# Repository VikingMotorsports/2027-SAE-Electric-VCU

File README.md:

# Formula SAE EV Vehicle Control System

A distributed **Vehicle Control System (VCS)** for a Formula SAE Electric racecar. The system uses STM32 microcontrollers running Zephyr RTOS for real-time vehicle control, a CAN bus for communication, and a Raspberry Pi for driver and remote telemetry displays.

> **Status:** Active Development

---

## System Overview

The VCS is currently built around two **STM32C092** modules and a Raspberry Pi.

- **Pedal Input Module** — Reads accelerator and brake pedal inputs and transmits them over CAN.
- **Motor Controller Module** — Receives pedal commands over CAN and generates PWM signals for the motor H-bridge.
- **Raspberry Pi Dashboard** — Receives CAN data and displays accelerator and brake inputs to the driver.
- **Remote Pit Dashboard** — Receives vehicle data from the Raspberry Pi over MQTT.

### Architecture

```text

     ┌──────────────────────┐			┌──────────────────────┐
     │   Brake Pedal        │			│   Accelerator Pedal  │
     └──────────┬───────────┘			└──────────┬───────────┘
				│								   │
				└─────────────────┬────────────────┘
                                  │
                                  ▼
                    ┌──────────────────────────┐
                    │   STM32C092              │
                    │   Pedal Input Module     │
                    │                          │
                    │   Zephyr RTOS            │
                    │   ADC → CAN              │
                    └────────────┬─────────────┘
                                 │
                                 │ CAN Bus
                                 │
                ┌────────────────┴────────────────┐
                │                                 │
                ▼                                 ▼
     ┌──────────────────────┐          ┌──────────────────────┐
     │   STM32C092          │          │   Raspberry Pi       │
     │   Motor Controller   │          │   Dashboard          │
     │                      │          │                      │
     │   CAN → PWM          │          │   CAN → Display      │
     └──────────┬───────────┘          └──────────┬───────────┘
                │                                 │
                │ PWM / Control                   │ MQTT
                ▼                                 ▼
     ┌──────────────────────┐          ┌──────────────────────┐
     │   Motor H-Bridge     │          │   Remote Pit         │
     │                      │          │   Dashboard          │
     └──────────────────────┘          └──────────────────────┘

````

---

## Hardware & Software

| Component        | Description                                                |
| ---------------- | ---------------------------------------------------------- |
| **STM32C092**    | Embedded vehicle control modules                           |
| **Zephyr RTOS**  | Real-time operating system for STM32 modules               |
| **CAN Bus**      | Communication between vehicle modules                      |
| **Raspberry Pi** | Dashboard and vehicle telemetry gateway                    |
| **Vulcan**       | CAN interface between the vehicle network and Raspberry Pi |
| **MQTT**         | Remote telemetry communication                             |
| **KiCad**        | Electrical and PCB design                                  |

---

## Repository Structure

```text
.
├── Dashboard/              # Raspberry Pi driver dashboard
├── Dashboard Webdisplay/   # Remote pit dashboard
├── Developers_Guide/       # Development documentation
├── PCB/                  	# PCB and electrical design files
├── MQTT/                   # MQTT communication
├── Vulcan/                 # CAN interface and configuration
├── Zephyr_apps/            # STM32C092 Zephyr applications
├── Zephyr_Scripts/         # Build, flash, and development scripts
├── .gitignore
└── README.md
```

---

## Communication

### CAN

The STM32 modules communicate over CAN. The Pedal Input Module sends accelerator and brake values to the CAN network, where they are received by the Motor Controller Module and Raspberry Pi.

```text
Pedal Module
     │
     ├── Accelerator
     └── Brake
          │
          ▼
       CAN Bus
       ┌────┴────┐
       ▼         ▼
Motor Controller  Raspberry Pi
       │             │
       ▼             ├──> Driver Dashboard
    PWM              │
       │             └──> MQTT
       ▼                    │
   H-Bridge                 ▼
                     Remote Pit Dashboard
```

### MQTT

The Raspberry Pi republishes selected CAN data over MQTT, allowing the pit crew to monitor vehicle information remotely.

---

## Current Functionality

The current system provides an end-to-end control and telemetry path:

* Accelerator and brake inputs are read by the Pedal Input Module.
* Pedal values are transmitted over CAN.
* The Motor Controller receives the commands and generates PWM output.
* The Raspberry Pi receives and displays pedal data on the driver dashboard.
* The Raspberry Pi broadcasts the same data over MQTT.
* A remote pit dashboard displays the transmitted vehicle data.

---

## Development

The system is designed to be modular, allowing additional vehicle control and monitoring functionality to be added as development continues.

### Planned Development

* [ ] Expand vehicle telemetry
* [ ] Add additional CAN messages
* [ ] Expand driver dashboard
* [ ] Expand remote pit monitoring
* [ ] Implement fault detection and reporting
* [ ] Add vehicle safety interlocks
* [ ] Develop dedicated VCS hardware
* [ ] Improve CAN diagnostics and logging
* [ ] Complete system-level testing

---

## Project Status

**Early Development / System Integration**

The basic vehicle control and telemetry pipeline is currently operational:

```text
Pedals
  ↓
STM32 Pedal Module
  ↓
CAN Bus
  ├──> STM32 Motor Controller ──> PWM ──> H-Bridge
  │
  └──> Raspberry Pi
          ├──> Driver Dashboard
          │
          └──> MQTT ──> Remote Pit Dashboard
```

Developed as part of a **Formula SAE Electric** racecar project.

```
```

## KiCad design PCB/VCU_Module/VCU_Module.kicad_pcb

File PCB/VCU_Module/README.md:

---
title: "**Viking MotorSports VCU Module**"
subtitle: |
  **Fabrication and Assembly Information**\
  For build TIME-STAMP
fontsize: 10pt
geometry:
  - margin=0.5in
toc: true
toc-depth: 2
colorlinks: true
urlcolor: blue
---

\newpage

# About this Board

## Board Description

## Documentation Links

## Documentation Files

| Filename                        | Notes                                    |
| ------------------------------- | ---------------------------------------- |
| README.pdf                      | This README file                         |
| VCU_Module-outline.dxf        | Board outline (with holes) in DXF format |
| VCU_Module-pcba.step          | 3D model of PCBA (with components)       |
| VCU_Module-render-bot.jpg     | Render of the top of the 3D model        |
| VCU_Module-render-bot.jpg     | Render of the bottom of the 3D model     |
| VCU_Module-schematic.pdf      | PDF of board schematics                  |

## Contact Information

- Website: *website*
- Email: *email*

## Board Renders

\newpage

# Printed Circuit Board (PCB) Fabrication Information

## Board Info

- 2 layer board
- Bounding box is *TBD*
- Board thickness is 1.59 mm (0.063 inch)

## Board Requirements

- Design Rules
    - Minimum Trace / Space design rulea: 0.1524 mm (6.0 mil) / 0.1524 mm (6.0 mil)
    - Outer dimension router tolerance: +/- 0.254 mm (10.0 mil)
    - Hole placement tolerance: +/- 0.075 mm (3.0 mil)
- Drills
   - Drill Positional Tolerance: 0.051 mm (2.0 mil)
   - Drill Size tolerance: +/- 0.064 mm (2.5 mil)
- Plated/Un-plated holes
  - There are no un-plated (NPT) holes
  - There are 96 plated through (PTH) holes
  - PTH minimum diameter: 0.254 mm (10 mil)
  - PTH minimum annulus: 0.102 mm (4 mil) radius
- Outline/Routing
  - No requirements.
- Slots
  - There are no slots.
- Cutouts
  - There are no cutouts
- There are 3 fiducials on the top layer.
- Panel tabs ("mouse bites")
   - Card edges must be smooth; no mouse bites or other intrusions into the card outline.
   - If external mouse bites are required, minimize and customer will remove by hand before assembly.
- If not otherwise specified, build to IPC 6012 Class 2 or better.

## Materials

- No requirements for materials.
- Copper Surface treatment should be ENIG, althogh immersion Silver is acceptable.
- White silkscreen on top and bottom surface
- Taiyo PSR-4000 or equivalent soldermask on top and bottom, no requirements for color.

## Stack Up

- Any FR4 like material is acceptable.
- 1 oz Copper on top and bottom layers
- 1.6 mm thick when done (1/16 inch)

## Array / Panel Information

- Coordinate with Contract Manufacturer (CM) for optimal size of this panel.
- If no feedback from CM, then produce single boards (no panel).

## Fabrication Files

### IPC-2581 File

| Filename                 | Notes                                   |
| ------------------------ | --------------------------------------- |
| VCU_Module-ipc2581.xml | IPC-2581 board information file         |

### Legacy PCB Files

| Filename                      | Notes                                         |
| ------------------------------| --------------------------------------------- |
| VCU_Module-Edge_Cuts.gbr    | RS274X file for the dimension (outline) layer |
| VCU_Module-F_Silkscreen.gbr | RS274X file for the top silkscreen            |
| VCU_Module-F_Mask.gbr       | RS274X file for the top soldermask            |
| VCU_Module-F_Cu.gbr         | RS274X file for the top copper layer          |
| VCU_Module-In1_Cu.gbr       | RS274X file for the layer 2 copper            |
| VCU_Module-In2_Cu.gbr       | RS274X file for the layer 3 copper            |
| VCU_Module-B_Cu.gbr         | RS274X file for the bottom copper layer       |
| VCU_Module-B_Mask.gbr       | RS274X file for the bottom soldermask         |
| VCU_Module-B_Silkscreen.gbr | RS274X file for the bottom silkscreen         |
| VCU_Module-NPTH.drl         | Excellon file for non-plated through holes    |
| VCU_Module-PTH.drl          | Excellon file for plated through holes        | 

\newpage

# Printed Circuit Board Assembly (PCBA) Information

## Assembly Info

- All components are on the top side of the board.
- This PCBA has two components that are SMT components with through-hole mechanical leads.

## Assembly Requirements

- Assemble to IPC Class 2 or better
- Solder paste can be ROHS or leaded.
- No clean, or Aqueous flux and wash, can be used.
- No conformal coating.

## Component Specific Assembly Information

- None

## Assembly Files

### IPC-2581 File

| Filename                 | Notes                           |
| ------------------------ | ------------------------------- |
| VCU_Module-ipc2581.xml | IPC-2581 board information file |

### Bill of Materials (BOM)

| Filename             | Description                            |
| -------------------- | -------------------------------------- |
| VCU_Module-bom.csv | BOM in Comma Separated Variable format |

### Solder Paste Stencils

| Filename                 | Notes                                            |
| ------------------------ | ------------------------------------------------ |
| VCU_Module-B_Paste.gbr | RS274X file for top/front solder paste stencil   |
| VCU_Module-F_Paste.gbr | RS274X file for bottom/back solder paste stencil |

### Mounting/Placement Location

| Filename            | Description                                 |
| ------------------- | ------------------------------------------- |
| VCU_Module-3u.pos | Pick and place locations for components     |

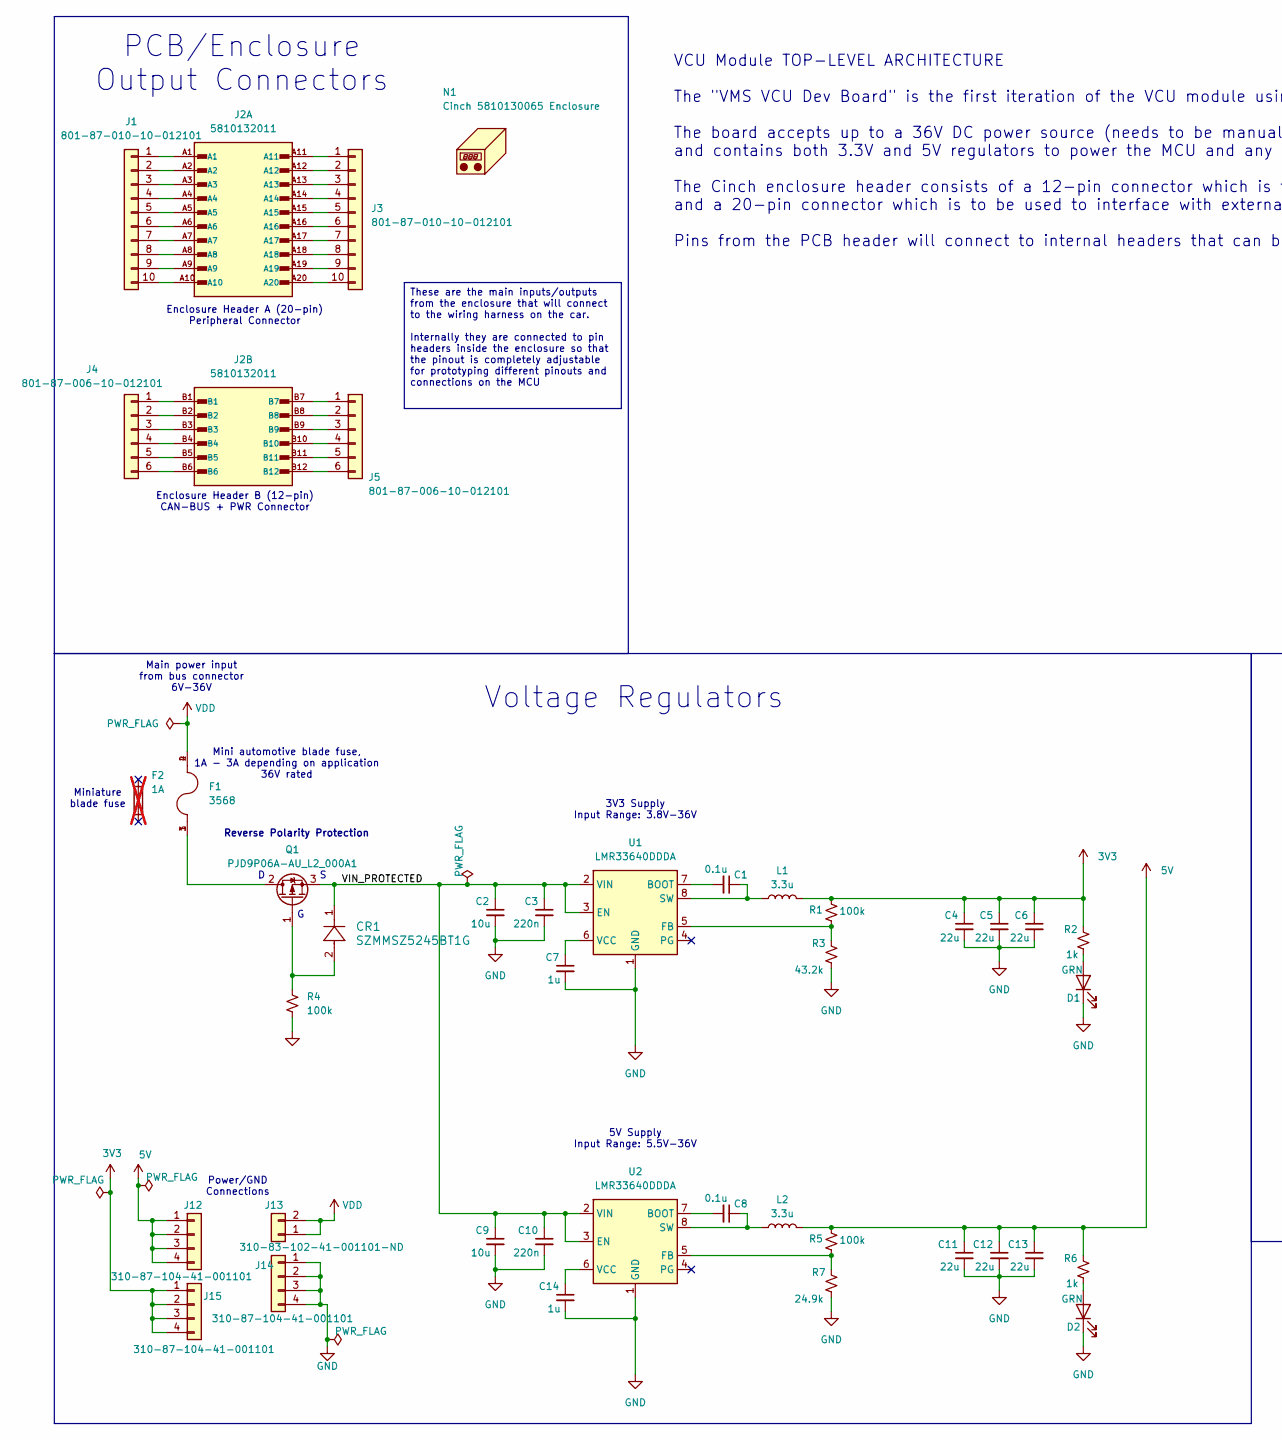
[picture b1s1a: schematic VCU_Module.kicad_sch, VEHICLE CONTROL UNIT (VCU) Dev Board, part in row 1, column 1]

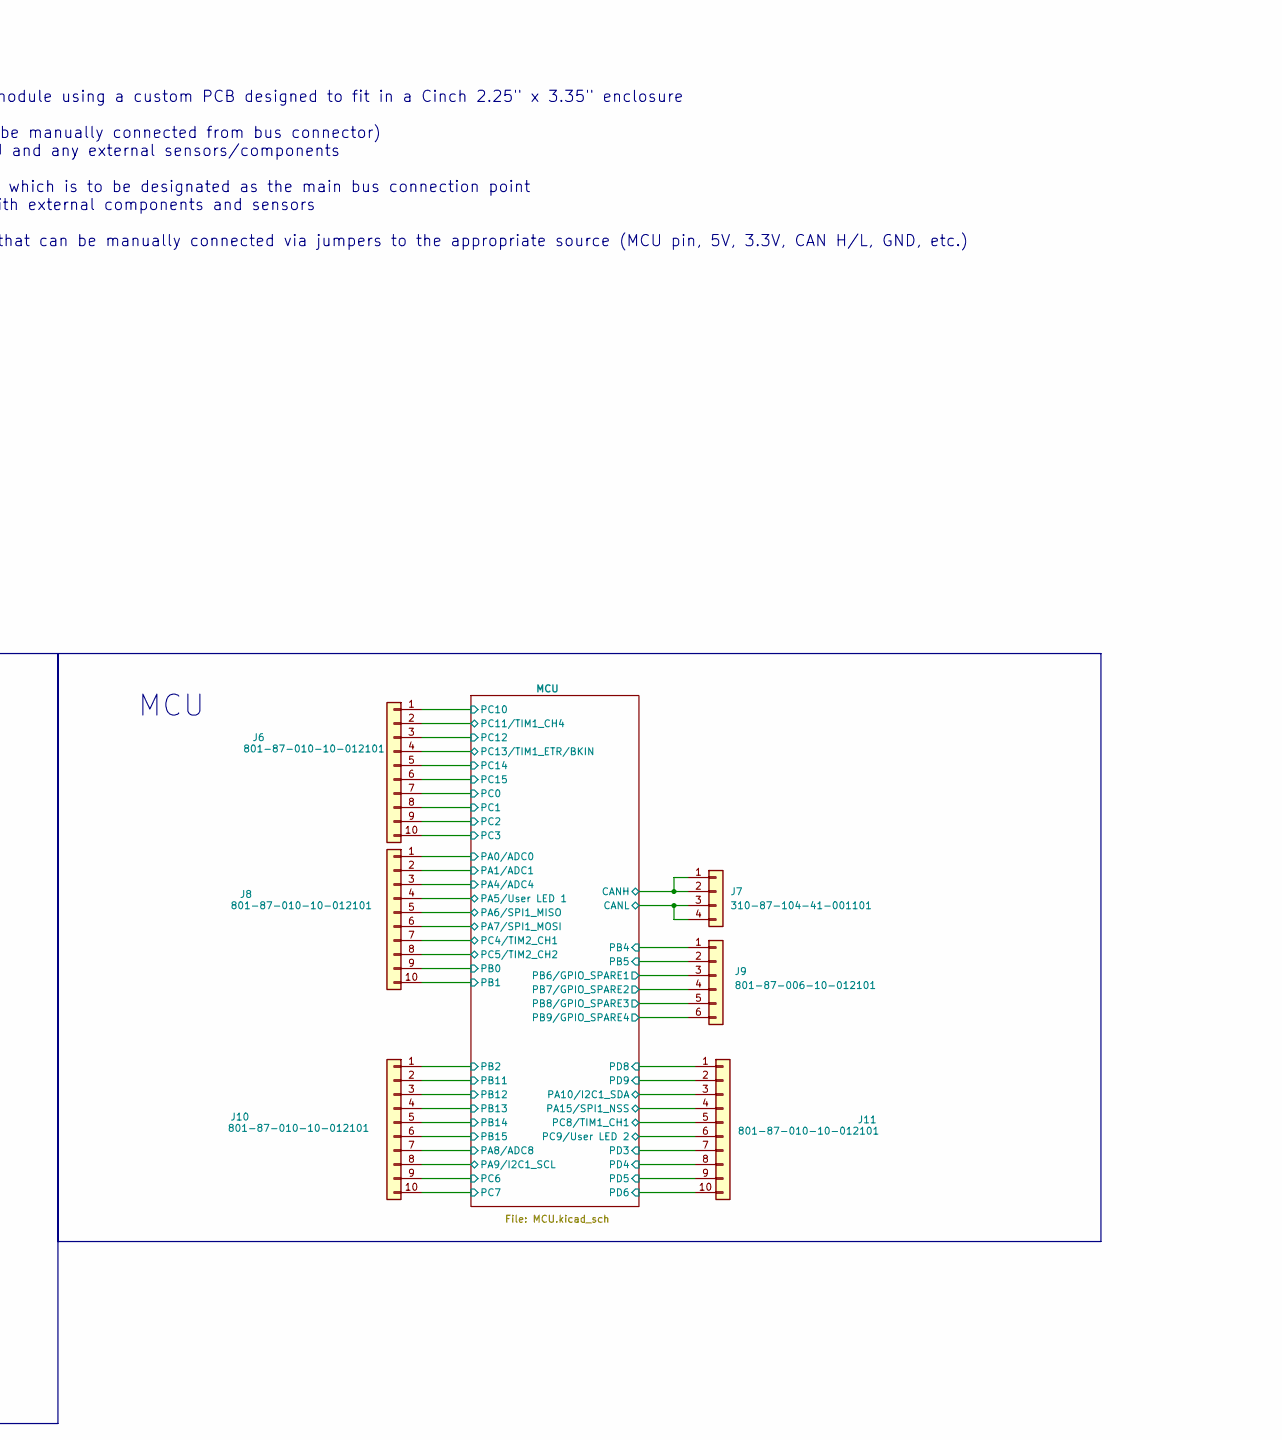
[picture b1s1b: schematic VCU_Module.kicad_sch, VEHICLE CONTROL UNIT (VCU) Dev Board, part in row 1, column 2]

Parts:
C1, C8: 0.1u; C_0805_2012Metric; MPN GCJ21BR72A104KA01L
C2, C9: 10u; C_0805_2012Metric; MPN GRT21BR61H475KE13L
C3, C10: 220n; C_0805_2012Metric; MPN CL21B224KBFVPNE
C4, C5, C6, C11, C12, C13: 22u; C_0805_2012Metric; MPN GRT21BR61C226ME13K
C7, C14: 1u; C_0805_2012Metric; MPN CGA4J3X7S2A105K125AB
CR1: SZMMSZ5245BT1G; SOD123_DIO; MPN SZMMSZ5245BT1G
D1, D2: GRN; LED_0805_2012Metric_Pad1.15x1.40mm_HandSolder; MPN SMLMN2ECTT86C
F1: 3568; FUSE_3568; PARTREV C
F2: 1A; Fuse_Blade_Mini_directSolder; not fitted
J1, J3, J6, J8, J10, J11: 801-87-010-10-012101; 1x10_Header_f; MPN 801-87-010-10-012101
J2: 5810132011; Cinch_5810132011_PCB_Header; PARTREV B
J4, J5, J9: 801-87-006-10-012101; PinHeader_1x06_P2.54mm_Vertical; MPN 801-87-006-10-012101
J7, J12, J14, J15: 310-87-104-41-001101; PinHeader_1x04_P2.54mm_Vertical; MPN 310-87-104-41-001101
J13: 310-83-102-41-001101-ND; PinHeader_1x02_P2.54mm_Vertical; MPN 310-83-102-41-001101
L1, L2: 3.3u; L_0805_2012Metric_Pad1.05x1.20mm_HandSolder; MPN AKPB002012103R3MA2
N1: Cinch 5810130065 Enclosure; SIP9_Housing; MPN 5810130065
Q1: PJD9P06A-AU_L2_000A1; TO-252-2; MPN PJD9P06A-AU_L2_000A1
R1, R4, R5: 100k; R_0805_2012Metric; MPN SG73S2ATTD1003F
R2, R6: 1k; R_0805_2012Metric; MPN SG73S2ATTD1001F
R3: 43.2k; R_0805_2012Metric; MPN RK73H2ATTD4322F
R7: 24.9k; R_0805_2012Metric; MPN RK73H2ATTD2492F
U1, U2: LMR33640DDDA; Texas_HSOP-8-1EP_3.9x4.9mm_P1.27mm_ThermalVias; MPN LMR33640DDDAR

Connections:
3V3: C4.1, C5.1, C6.1, J15.1, J15.2, J15.3, J15.4, L1.2, R1.2, R2.2; also elsewhere on the board
5V: C11.1, C12.1, C13.1, J12.1, J12.2, J12.3, J12.4, L2.2, R5.2, R6.2; also elsewhere on the board
/MCU/CANH: J7.1, J7.2; also elsewhere on the board
/MCU/CANL: J7.3, J7.4; also elsewhere on the board
/MCU/PA0/ADC0: J8.1; also elsewhere on the board
/MCU/PA1/ADC1: J8.2; also elsewhere on the board
/MCU/PA4/ADC4: J8.3; also elsewhere on the board
/MCU/PA5/User LED 1: J8.4; also elsewhere on the board
/MCU/PA6/SPI1_MISO: J8.5; also elsewhere on the board
/MCU/PA7/SPI1_MOSI: J8.6; also elsewhere on the board
/MCU/PA8/ADC8: J10.7; also elsewhere on the board
/MCU/PA9/I2C1_SCL: J10.8; also elsewhere on the board
/MCU/PA10/I2C1_SDA: J11.3; also elsewhere on the board
/MCU/PA15/SPI1_NSS: J11.4; also elsewhere on the board
/MCU/PB0: J8.9; also elsewhere on the board
/MCU/PB1: J8.10; also elsewhere on the board
/MCU/PB2: J10.1; also elsewhere on the board
/MCU/PB4: J9.1; also elsewhere on the board
/MCU/PB5: J9.2; also elsewhere on the board
/MCU/PB6/GPIO_SPARE1: J9.3; also elsewhere on the board
/MCU/PB7/GPIO_SPARE2: J9.4; also elsewhere on the board
/MCU/PB8/GPIO_SPARE3: J9.5; also elsewhere on the board
/MCU/PB9/GPIO_SPARE4: J9.6; also elsewhere on the board
/MCU/PB11: J10.2; also elsewhere on the board
/MCU/PB12: J10.3; also elsewhere on the board
/MCU/PB13: J10.4; also elsewhere on the board
/MCU/PB14: J10.5; also elsewhere on the board
/MCU/PB15: J10.6; also elsewhere on the board
/MCU/PC0: J6.7; also elsewhere on the board
/MCU/PC1: J6.8; also elsewhere on the board
/MCU/PC2: J6.9; also elsewhere on the board
/MCU/PC3: J6.10; also elsewhere on the board
/MCU/PC4/TIM2_CH1: J8.7; also elsewhere on the board
/MCU/PC5/TIM2_CH2: J8.8; also elsewhere on the board
/MCU/PC6: J10.9; also elsewhere on the board
/MCU/PC7: J10.10; also elsewhere on the board
/MCU/PC8/TIM1_CH1: J11.5; also elsewhere on the board
/MCU/PC9/User LED 2: J11.6; also elsewhere on the board
/MCU/PC10: J6.1; also elsewhere on the board
/MCU/PC11/TIM1_CH4: J6.2; also elsewhere on the board
/MCU/PC12: J6.3; also elsewhere on the board
/MCU/PC13/TIM1_ETR/BKIN: J6.4; also elsewhere on the board
/MCU/PC14: J6.5; also elsewhere on the board
/MCU/PC15: J6.6; also elsewhere on the board
/MCU/PD3: J11.7; also elsewhere on the board
/MCU/PD4: J11.8; also elsewhere on the board
/MCU/PD5: J11.9; also elsewhere on the board
/MCU/PD6: J11.10; also elsewhere on the board
/MCU/PD8: J11.1; also elsewhere on the board
/MCU/PD9: J11.2; also elsewhere on the board
/VIN_PROTECTED: C2.1, C3.1, C9.1, C10.1, CR1.1, Q1.3 (S), U1.2 (VIN), U1.3 (EN), U2.2 (VIN), U2.3 (EN)
GND: C2.2, C3.2, C4.2, C5.2, C6.2, C7.2, C9.2, C10.2, C11.2, C12.2, C13.2, C14.2, D1.1 (K), D2.1 (K), J14.1, J14.2, J14.3, J14.4, R3.1, R4.2, R7.1, U1.1 (GND), U1.9 (GND), U2.1 (GND), U2.9 (GND); also elsewhere on the board
unnamed: D1.2 (A), R2.1
unnamed: D2.2 (A), R6.1
unnamed: J1.1, J2.A1
unnamed: J1.2, J2.A2
unnamed: J1.3, J2.A3
unnamed: J1.4, J2.A4
unnamed: J1.5, J2.A5
unnamed: J1.6, J2.A6
unnamed: J1.7, J2.A7
unnamed: J1.8, J2.A8
unnamed: J1.9, J2.A9
unnamed: J1.10, J2.A10
unnamed: J2.A11, J3.1
unnamed: J2.A12, J3.2
unnamed: J2.A13, J3.3
unnamed: J2.A14, J3.4
unnamed: J2.A15, J3.5
unnamed: J2.A16, J3.6
unnamed: J2.A17, J3.7
unnamed: J2.A18, J3.8
unnamed: J2.A19, J3.9
unnamed: J2.A20, J3.10
unnamed: J2.B1, J4.1
unnamed: J2.B2, J4.2
unnamed: J2.B3, J4.3
unnamed: J2.B4, J4.4
unnamed: J2.B5, J4.5
unnamed: J2.B6, J4.6
unnamed: J2.B7, J5.1
unnamed: J2.B8, J5.2
unnamed: J2.B9, J5.3
unnamed: J2.B10, J5.4
unnamed: J2.B11, J5.5
unnamed: J2.B12, J5.6
unnamed: F1.1, F1.3, Q1.2 (D)
unnamed: CR1.2, Q1.1 (G), R4.1
unnamed: C1.2, U1.7 (BOOT)
unnamed: R1.1, R3.2, U1.5 (FB)
unnamed: C1.1, L1.1, U1.8 (SW)
unnamed: C7.1, U1.6 (VCC)
unnamed: C8.2, U2.7 (BOOT)
unnamed: R5.1, R7.2, U2.5 (FB)
unnamed: C8.1, L2.1, U2.8 (SW)
unnamed: C14.1, U2.6 (VCC)
VDD: F1.2, F1.4, J13.1, J13.2

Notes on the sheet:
Reverse Polarity Protection
Enclosure Header B (12-pin) CAN-BUS + PWR Connector
5V Supply Input Range: 5.5V-36V
Main power input from bus connector 6V-36V
3V3 Supply Input Range: 3.8V-36V
PCB/Enclosure Output Connectors
MCU
Power/GND Connections
Mini automotive blade fuse, 1A - 3A depending on application 36V rated
Miniature blade fuse
VCU Module TOP-LEVEL ARCHITECTURE The "VMS VCU Dev Board" is the first iteration of the VCU module using a custom PCB designed to fit in a Cinch 2.25" x 3.35" enclosure The board accepts up to a 36V DC power source (needs to be manually connected from bus connector) and contains both 3.3V and 5V re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
Enclosure Header A (20-pin) Peripheral Connector
Voltage Regulators
These are the main inputs/outputs from the enclosure that will connect to the wiring harness on the car. Internally they are connected to pin headers inside the enclosure so that the pinout is completely adjustable for prototyping different pinouts and connections on the MCU

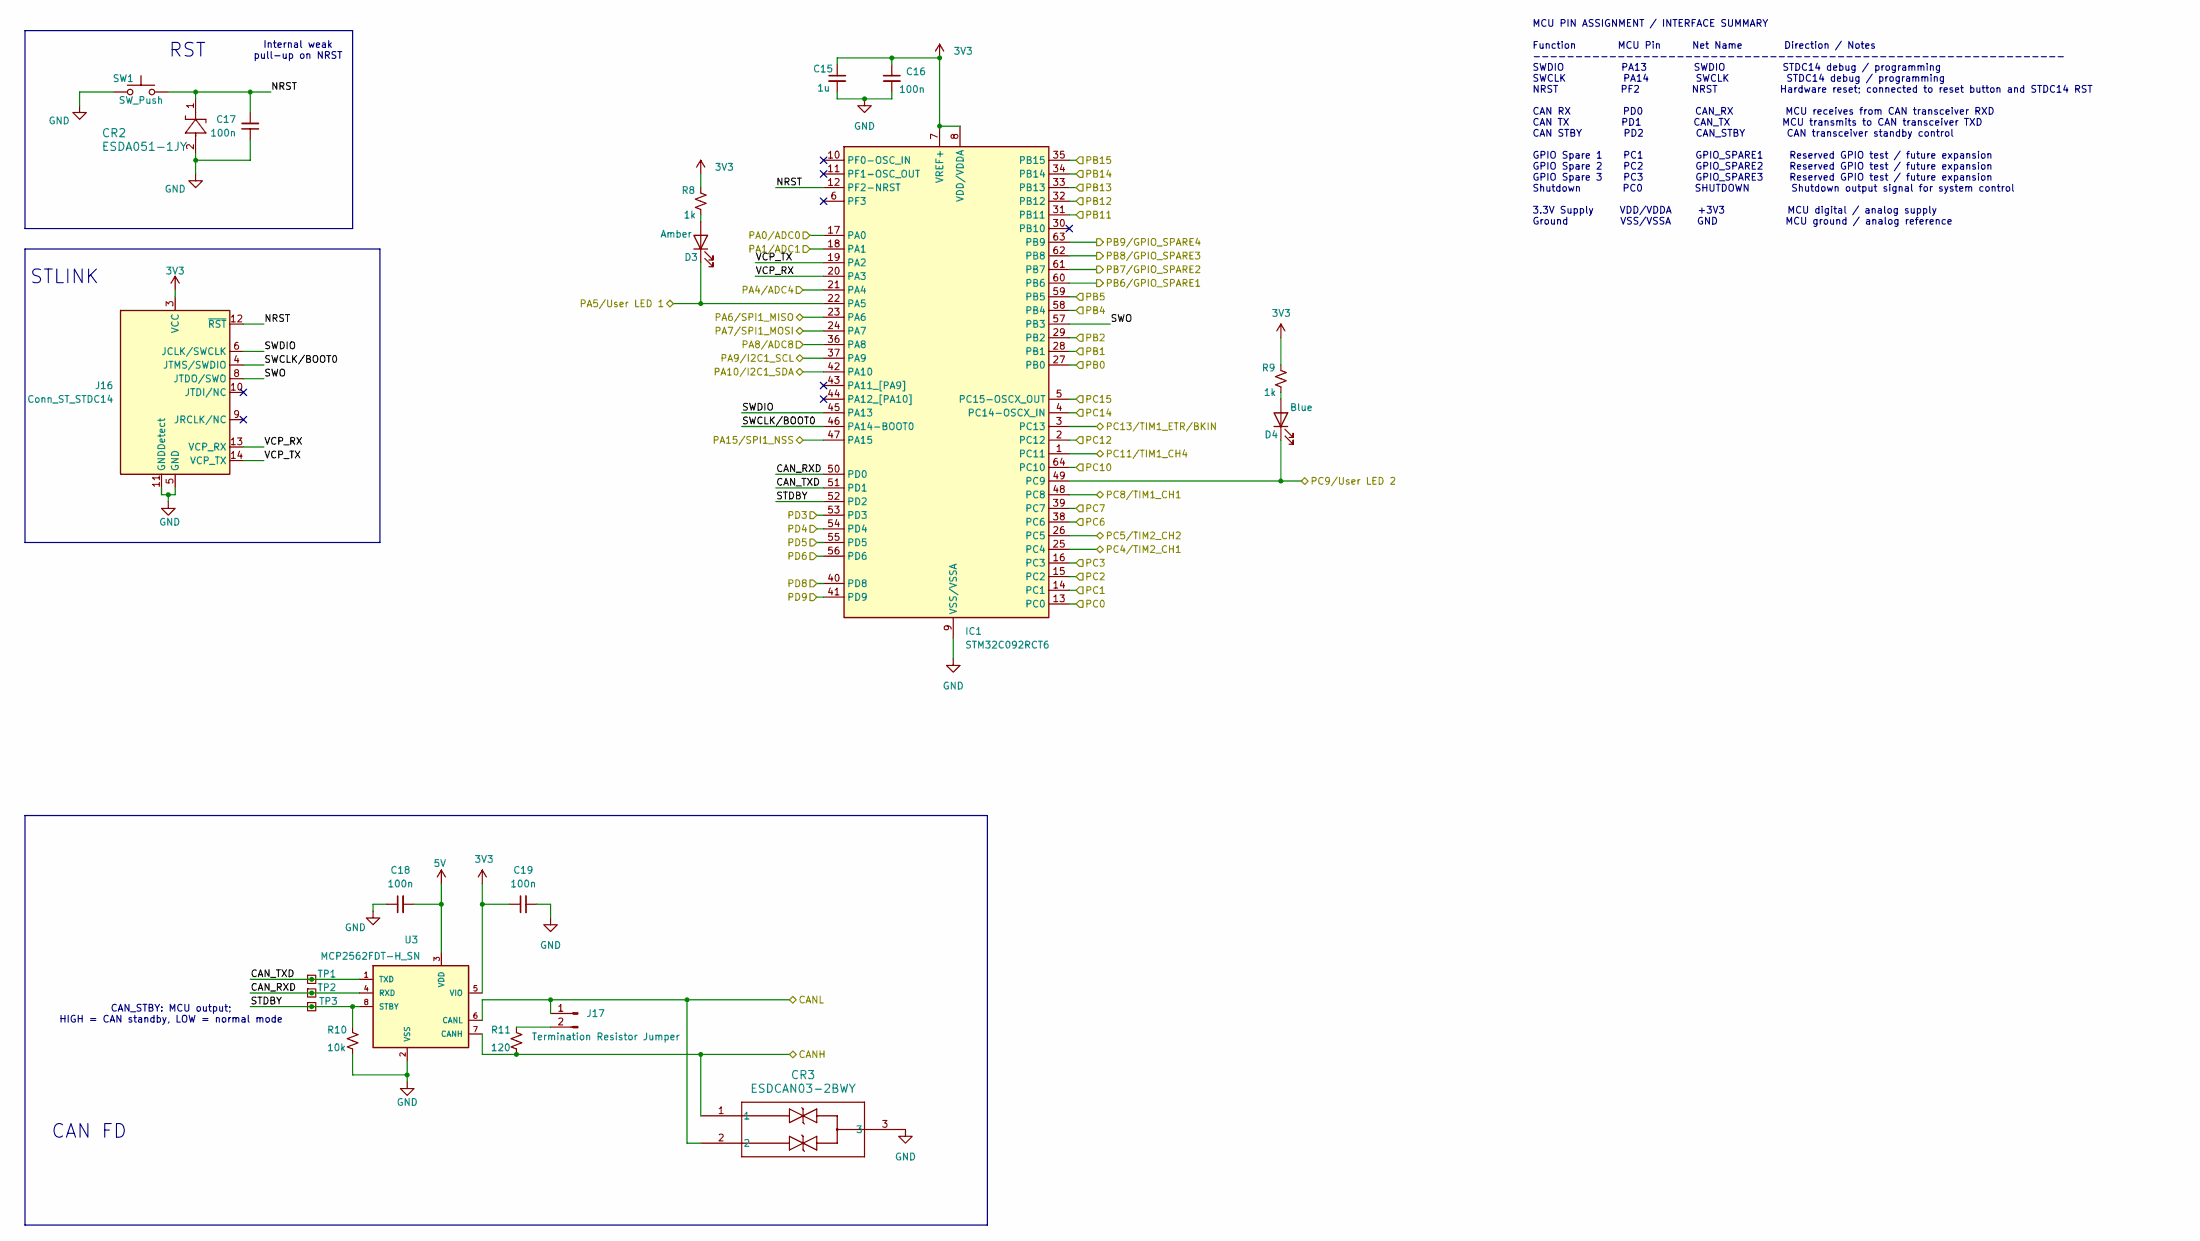
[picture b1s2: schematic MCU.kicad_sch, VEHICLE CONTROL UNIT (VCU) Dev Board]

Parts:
C15: 1u; C_0805_2012Metric; MPN CGA4J3X7S2A105K125AB
C16, C17, C18, C19: 100n; C_0805_2012Metric; MPN GCJ21BR72A104KA01L
CR2: ESDA051-1JY; D_SOD-323; MPN ESDA051-1JY
CR3: ESDCAN03-2BWY; SOT323-3L_STM; MPN ESDCAN03-2BWY
D3: Amber; LED_0805_2012Metric_Pad1.15x1.40mm_HandSolder; MPN SML-H12D8TT86C
D4: Blue; LED_0805_2012Metric_Pad1.15x1.40mm_HandSolder; MPN SMLMN2BCTT86C
IC1: STM32C092RCT6; QFP50P1200X1200X160-64N; Manufacturer_Part_Number STM32C092RCT6; Mouser Part Number 511-STM32C092RCT6
J16: Conn_ST_STDC14; PinHeader_2x07_P1.27mm_Vertical; MPN FTSH-107-01-S-D-K
J17: Termination Resistor Jumper; PinHeader_1x02_P2.54mm_Vertical; MPN TS-102-T-A
R8, R9: 1k; R_0805_2012Metric; MPN SG73S2ATTD1001F
R10: 10k; R_0805_2012Metric; MPN SG73S2ATTD103J
R11: 120; R_0805_2012Metric; MPN SG73S2ATTD1200F
SW1: SW_Push; SW_PUSH_6mm_H4.3mm; MPN B3F-1000
TP1, TP2, TP3: TestPoint_Small; TestPoint_THTPad_D1.5mm_Drill0.7mm
U3: MCP2562FDT-H_SN; SOIC127P600X175-8N; MPN MCP2562FDT-H/SN

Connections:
3V3: C15.1, C16.1, C19.1, IC1.7 (VREF+), IC1.8 (VDD/VDDA), J16.3 (VCC), R8.2, R9.2, U3.5 (VIO); also elsewhere on the board
5V: C18.2, U3.3 (VDD); also elsewhere on the board
/MCU/CANH: CR3.1, R11.2, U3.7 (CANH); also elsewhere on the board
/MCU/CANL: CR3.2, J17.1, U3.6 (CANL); also elsewhere on the board
/MCU/CAN_RXD: IC1.50 (PD0), TP2.1 (1_1), U3.4 (RXD)
/MCU/CAN_TXD: IC1.51 (PD1), TP1.1 (1_1), U3.1 (TXD)
/MCU/NRST: C17.2, CR2.1, IC1.12 (PF2-NRST), J16.12 (~RST), SW1.1
/MCU/PA0/ADC0: IC1.17 (PA0); also elsewhere on the board
/MCU/PA1/ADC1: IC1.18 (PA1); also elsewhere on the board
/MCU/PA4/ADC4: IC1.21 (PA4); also elsewhere on the board
/MCU/PA5/User LED 1: D3.1 (K), IC1.22 (PA5); also elsewhere on the board
/MCU/PA6/SPI1_MISO: IC1.23 (PA6); also elsewhere on the board
/MCU/PA7/SPI1_MOSI: IC1.24 (PA7); also elsewhere on the board
/MCU/PA8/ADC8: IC1.36 (PA8); also elsewhere on the board
/MCU/PA9/I2C1_SCL: IC1.37 (PA9); also elsewhere on the board
/MCU/PA10/I2C1_SDA: IC1.42 (PA10); also elsewhere on the board
/MCU/PA15/SPI1_NSS: IC1.47 (PA15); also elsewhere on the board
/MCU/PB0: IC1.27 (PB0); also elsewhere on the board
/MCU/PB1: IC1.28 (PB1); also elsewhere on the board
/MCU/PB2: IC1.29 (PB2); also elsewhere on the board
/MCU/PB4: IC1.58 (PB4); also elsewhere on the board
/MCU/PB5: IC1.59 (PB5); also elsewhere on the board
/MCU/PB6/GPIO_SPARE1: IC1.60 (PB6); also elsewhere on the board
/MCU/PB7/GPIO_SPARE2: IC1.61 (PB7); also elsewhere on the board
/MCU/PB8/GPIO_SPARE3: IC1.62 (PB8); also elsewhere on the board
/MCU/PB9/GPIO_SPARE4: IC1.63 (PB9); also elsewhere on the board
/MCU/PB11: IC1.31 (PB11); also elsewhere on the board
/MCU/PB12: IC1.32 (PB12); also elsewhere on the board
/MCU/PB13: IC1.33 (PB13); also elsewhere on the board
/MCU/PB14: IC1.34 (PB14); also elsewhere on the board
/MCU/PB15: IC1.35 (PB15); also elsewhere on the board
/MCU/PC0: IC1.13 (PC0); also elsewhere on the board
/MCU/PC1: IC1.14 (PC1); also elsewhere on the board
/MCU/PC2: IC1.15 (PC2); also elsewhere on the board
/MCU/PC3: IC1.16 (PC3); also elsewhere on the board
/MCU/PC4/TIM2_CH1: IC1.25 (PC4); also elsewhere on the board
/MCU/PC5/TIM2_CH2: IC1.26 (PC5); also elsewhere on the board
/MCU/PC6: IC1.38 (PC6); also elsewhere on the board
/MCU/PC7: IC1.39 (PC7); also elsewhere on the board
/MCU/PC8/TIM1_CH1: IC1.48 (PC8); also elsewhere on the board
/MCU/PC9/User LED 2: D4.1 (K), IC1.49 (PC9); also elsewhere on the board
/MCU/PC10: IC1.64 (PC10); also elsewhere on the board
/MCU/PC11/TIM1_CH4: IC1.1 (PC11); also elsewhere on the board
/MCU/PC12: IC1.2 (PC12); also elsewhere on the board
/MCU/PC13/TIM1_ETR/BKIN: IC1.3 (PC13); also elsewhere on the board
/MCU/PC14: IC1.4 (PC14-OSCX_IN); also elsewhere on the board
/MCU/PC15: IC1.5 (PC15-OSCX_OUT); also elsewhere on the board
/MCU/PD3: IC1.53 (PD3); also elsewhere on the board
/MCU/PD4: IC1.54 (PD4); also elsewhere on the board
/MCU/PD5: IC1.55 (PD5); also elsewhere on the board
/MCU/PD6: IC1.56 (PD6); also elsewhere on the board
/MCU/PD8: IC1.40 (PD8); also elsewhere on the board
/MCU/PD9: IC1.41 (PD9); also elsewhere on the board
/MCU/STDBY: IC1.52 (PD2), R10.1, TP3.1 (1_1), U3.8 (STBY)
/MCU/SWCLK/BOOT0: IC1.46 (PA14-BOOT0), J16.4 (JTMS/SWDIO)
/MCU/SWDIO: IC1.45 (PA13), J16.6 (JCLK/SWCLK)
/MCU/SWO: IC1.57 (PB3), J16.8 (JTDO/SWO)
/MCU/VCP_RX: IC1.20 (PA3), J16.13 (VCP_RX)
/MCU/VCP_TX: IC1.19 (PA2), J16.14 (VCP_TX)
GND: C15.2, C16.2, C17.1, C18.1, C19.2, CR2.2, CR3.3, IC1.9 (VSS/VSSA), J16.5 (GND), J16.7 (GND), J16.11 (GNDDetect), R10.2, SW1.2, U3.2 (VSS); also elsewhere on the board
unnamed: D3.2 (A), R8.1
unnamed: D4.2 (A), R9.1
unnamed: J17.2, R11.1

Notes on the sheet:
MCU PIN ASSIGNMENT / INTERFACE SUMMARY Function MCU Pin Net Name Direction / Notes --------------------------------------------------------------- SWDIO PA13 SWDIO STDC14 debug / programming SWCLK PA14 SWCLK STDC14 debug / programming NRST PF2 NRST Hardware reset; connected to reset button and STDC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
STLINK
CAN FD
RST
CAN_STBY: MCU output; HIGH = CAN standby, LOW = normal mode
Internal weak pull-up on NRST

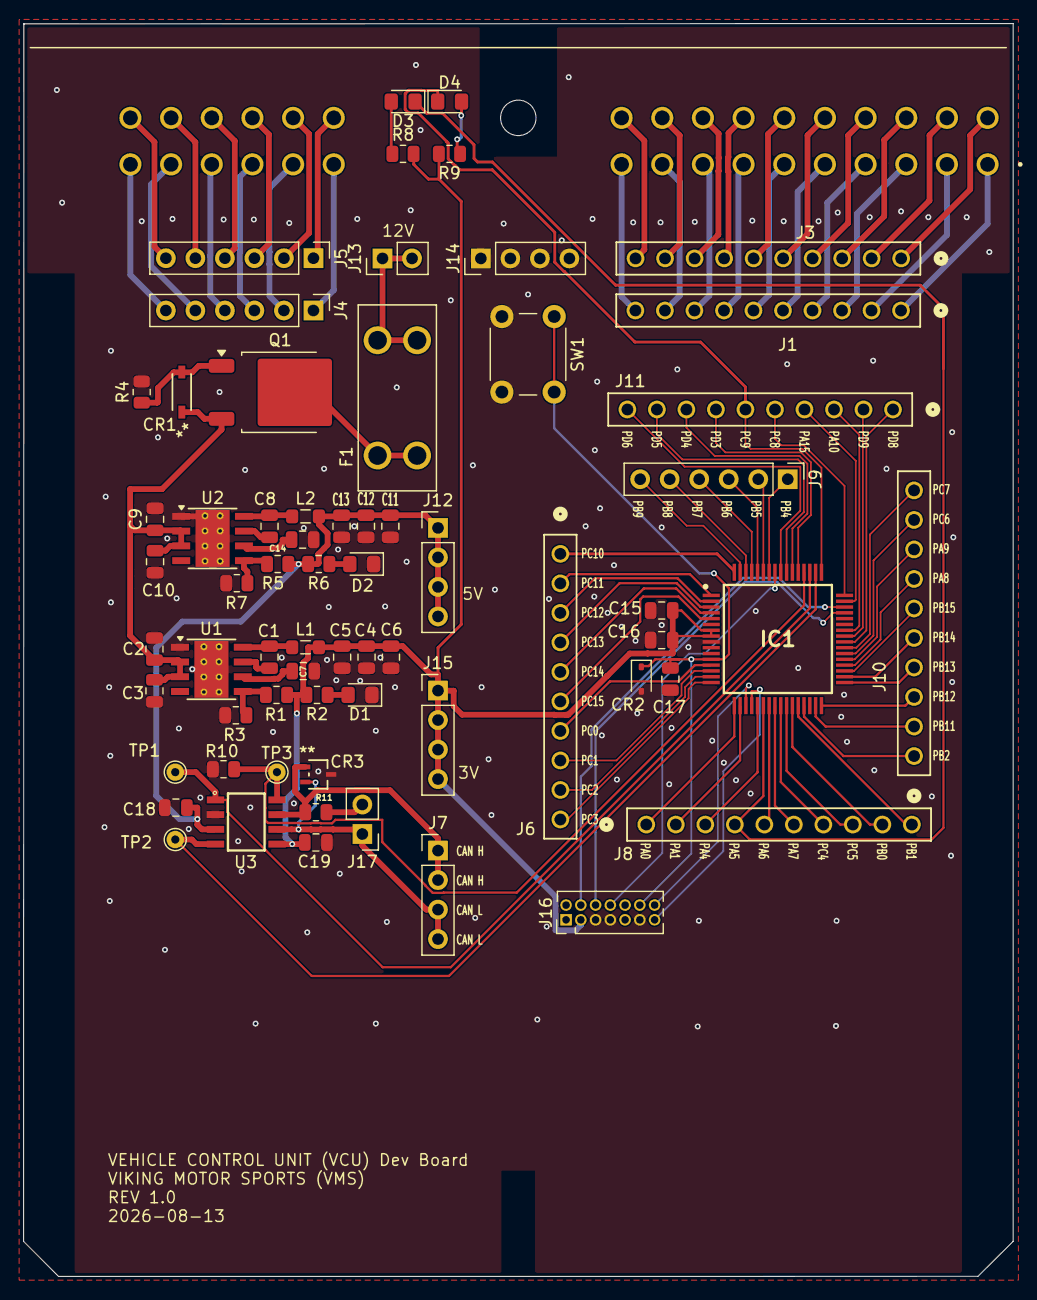
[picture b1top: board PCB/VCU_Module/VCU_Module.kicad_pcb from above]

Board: 2 copper layers, 85.2 x 107.8 mm, 66 parts (0 on the bottom side), 109 nets.
